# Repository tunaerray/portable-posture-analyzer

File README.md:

# Portable Posture & Balance Analyzer

A wearable device designed to monitor back and shoulder posture in real time, alerting the user via vibration and OLED display when poor posture is detected.

> **Work in Progress**  
> PCB design is complete. Firmware development is ongoing.

## Overview

This project is a health and ergonomics-focused embedded system that tracks posture using an IMU sensor. When poor posture is detected, the device triggers a vibration motor and displays a warning on the OLED screen. The system is built around the MSP430G2553 microcontroller.

## Components

- **MPU6050** - 6-axis IMU sensor (accelerometer + gyroscope)
- **Vibration Motor** - Haptic alert for poor posture
- **OLED Display** - Real-time posture score and warning display
- **HC-05 Bluetooth** - Daily report transmission
- **MSP430G2553** - Main microcontroller

## Pin Connections

- **MPU6050**
  - SCL -> P1.6
  - SDA -> P1.7

- **OLED Display**
  - SCL -> P1.6
  - SDA -> P1.7
  - Uses the same I2C bus as the MPU6050 with a different I2C address

- **Vibration Motor**
  - Control Pin -> P2.0

- **Bluetooth HC-05**
  - RX -> P1.2
  - TX -> P1.1

## How It Works

1. MPU6050 raw accelerometer and gyroscope data is read over I2C.
2. Angle calculation is performed using `atan2`.
3. A posture score is computed periodically using Timer_A.
4. If poor posture is detected, the vibration motor is activated.
5. The OLED display shows posture status and warning messages.
6. A daily posture report is sent via Bluetooth to a paired device.

## Project Status

- [x] PCB design complete
- [ ] Firmware development in progress
- [ ] Testing and calibration
- [ ] Enclosure design

## Images

### PCB Front

### PCB Back

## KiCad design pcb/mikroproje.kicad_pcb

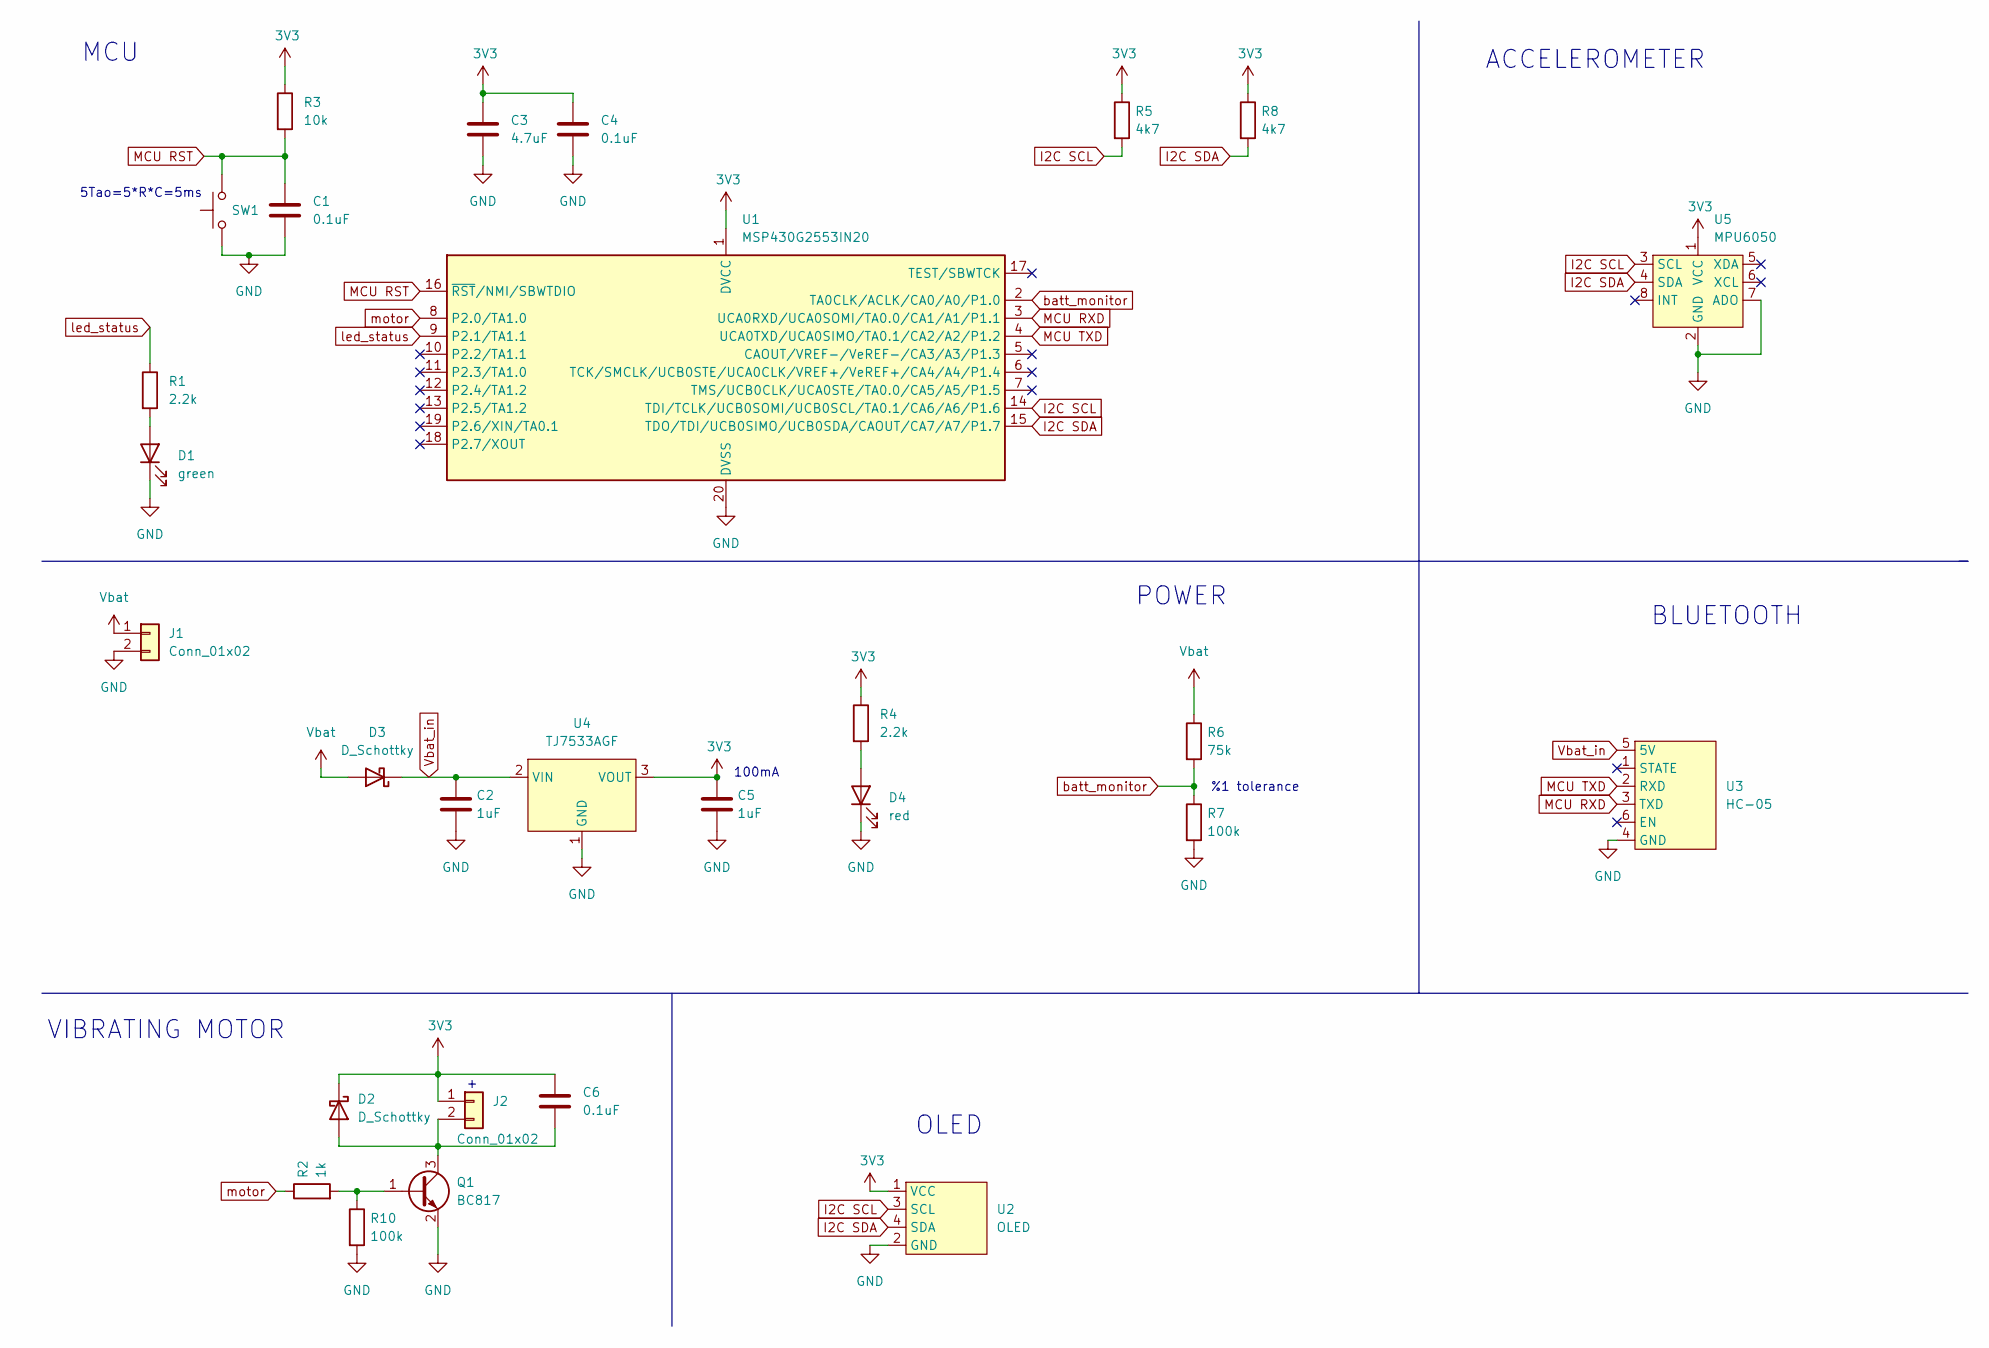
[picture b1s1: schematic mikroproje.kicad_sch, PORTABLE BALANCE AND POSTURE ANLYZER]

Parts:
C1: 0.1uF; C_1206_3216Metric
C2: 1uF; C_1206_3216Metric
C3: 4.7uF; C_1206_3216Metric_Pad1.33x1.80mm_HandSolder
C4, C6: 0.1uF; C_1206_3216Metric_Pad1.33x1.80mm_HandSolder
C5: 1uF; C_1206_3216Metric_Pad1.33x1.80mm_HandSolder
D1: green; LED_1206_3216Metric
D2, D3: D_Schottky; D_SOD-123
D4: red; LED_1206_3216Metric
J1: Conn_01x02; JST_PH_B2B-PH-K_1x02_P2.00mm_Vertical
J2: Conn_01x02; vibrator
Q1: BC817; SOT-23
R1, R4: 2.2k; R_1206_3216Metric
R2: 1k; R_1206_3216Metric
R3: 10k; R_1206_3216Metric
R5, R8: 4k7; R_1206_3216Metric
R6: 75k; R_1206_3216Metric
R7, R10: 100k; R_1206_3216Metric
SW1: SW_Push; SW_Push_1P1T_NO_CK_KSC7xxJ
U1: MSP430G2553IN20; DIP-20_W7.62mm
U2: OLED
U3: HC-05
U4: TJ7533AGF; SOT-89-3
U5: MPU6050; MPU6050_Module

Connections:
3V3: C3.1, C4.1, C5.1, C6.1, D2.1 (K), J2.1, R3.1, R4.1, R5.1, R8.1, U1.1 (DVCC), U2.1 (VCC), U4.3 (VOUT), U5.1 (VCC)
GND: C1.2, C2.2, C3.2, C4.2, C5.2, D1.1 (K), D4.1 (K), J1.2, Q1.2 (E), R7.2, R10.2, SW1.1, U1.20 (DVSS), U2.2 (GND), U3.4 (GND), U4.1 (GND), U5.2 (GND), U5.7 (ADO)
I2C SCL: R5.2, U1.14 (TDI/TCLK/UCB0SOMI/UCB0SCL/TA0.1/CA6/A6/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), U2.3 (SCL), U5.3 (SCL)
I2C SDA: R8.2, U1.15 (TDO/TDI/UCB0SIMO/UCB0SDA/CAOUT/CA7/A7/P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), U2.4 (SDA), U5.4 (SDA)
MCU RST: C1.1, R3.2, SW1.2, U1.16 (~RST/NMI/SBWTDIO)
MCU RXD: U1.3 (UCA0RXD/UCA0SOMI/TA0.0/CA1/A1/P1.1), U3.3 (TXD)
MCU TXD: U1.4 (UCA0TXD/UCA0SIMO/TA0.1/CA2/A2/P1.2), U3.2 (RXD)
unnamed: D1.2 (A), R1.2
unnamed: C6.2, D2.2 (A), J2.2, Q1.3 (C)
unnamed: D4.2 (A), R4.2
unnamed: Q1.1 (B), R2.2, R10.1
Vbat: D3.2 (A), J1.1, R6.1
Vbat_in: C2.1, D3.1 (K), U3.5 (5V), U4.2 (VIN)
batt_monitor: R6.2, R7.1, U1.2 (TA0CLK/ACLK/CA0/A0/P1.0)
led_status: R1.1, U1.9 (P2.1/TA1.1)
motor: R2.1, U1.8 (P2.0/TA1.0)

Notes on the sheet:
POWER
ACCELEROMETER
VIBRATING MOTOR
MCU
BLUETOOTH
%1 tolerance
OLED
100mA
5Tao=5*R*C=5ms

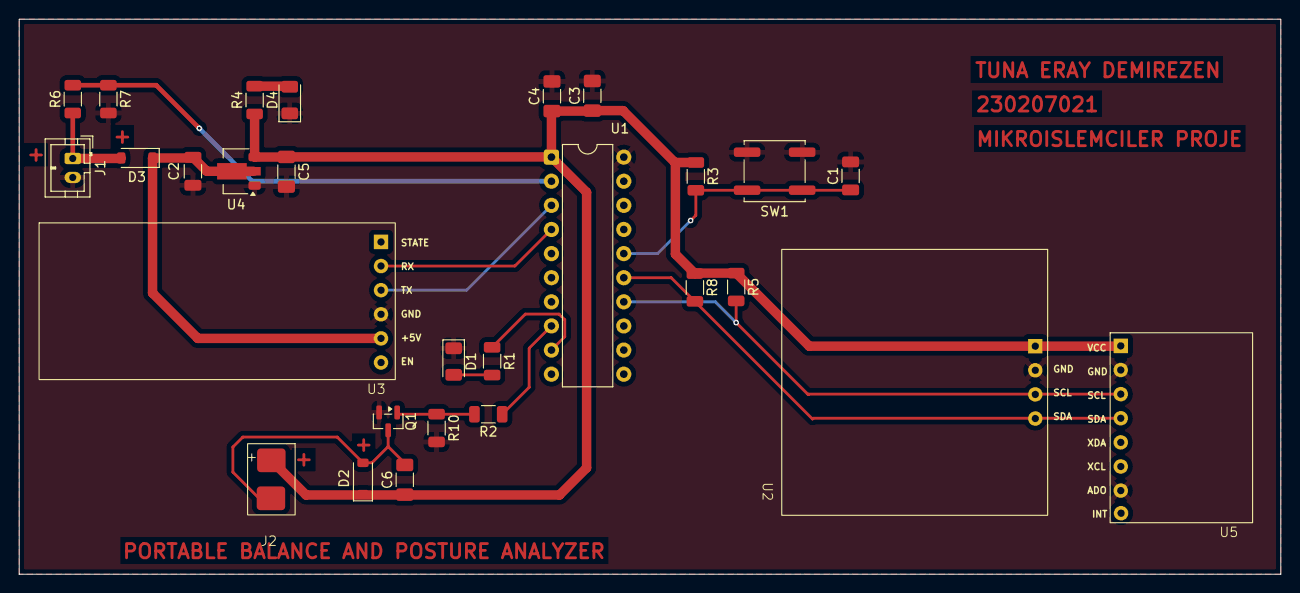
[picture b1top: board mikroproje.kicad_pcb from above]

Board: 2 copper layers, 132.8 x 58.5 mm, 28 parts (0 on the bottom side), 16 nets.
